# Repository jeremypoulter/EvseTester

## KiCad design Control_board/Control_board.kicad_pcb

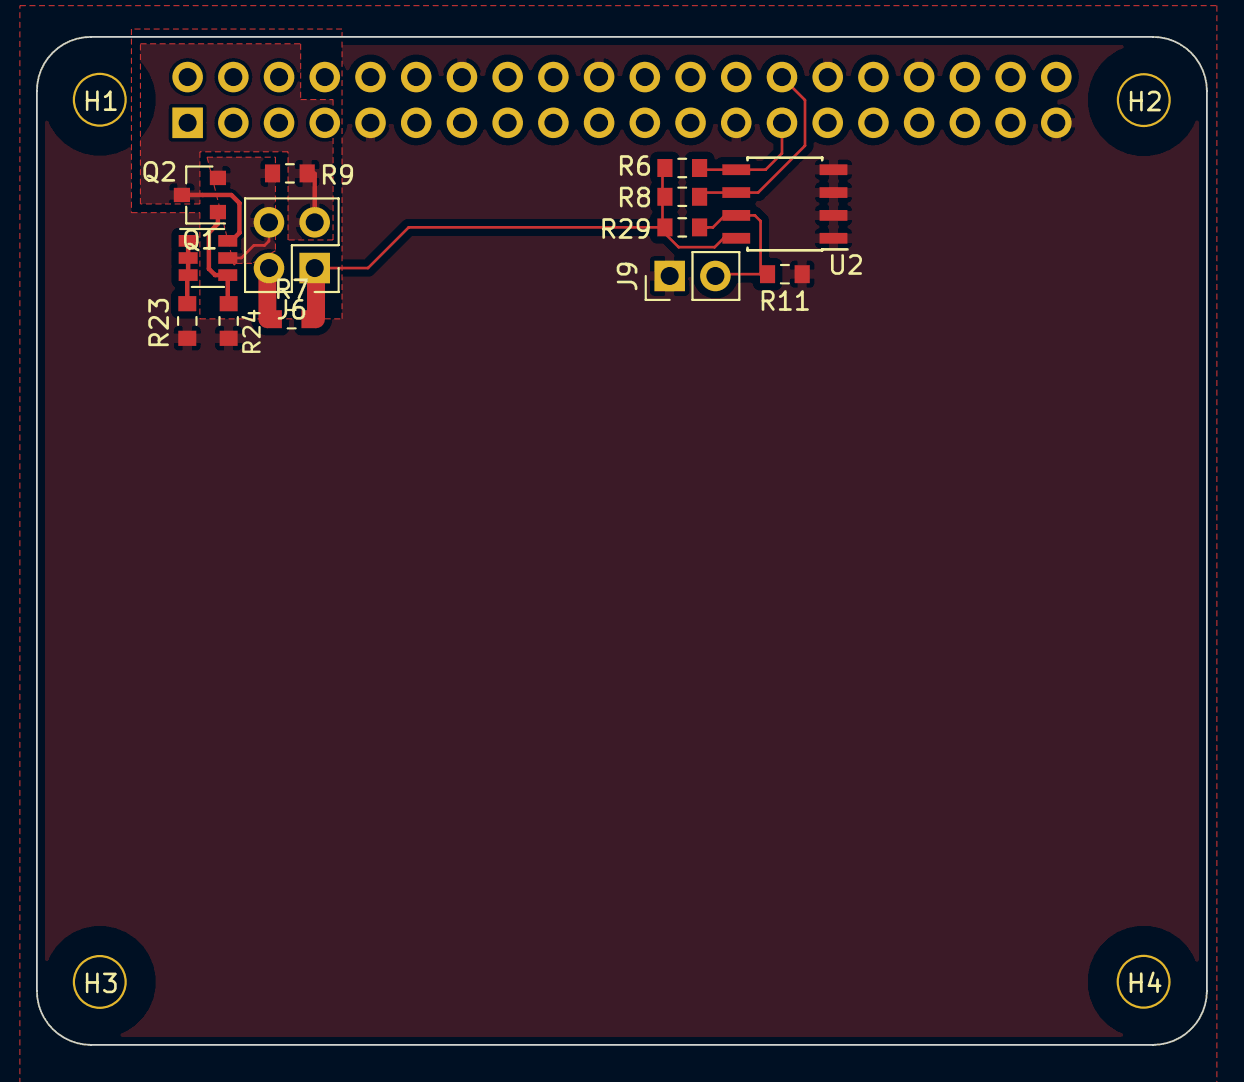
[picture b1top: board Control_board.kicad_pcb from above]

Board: 2 copper layers, 65.0 x 56.0 mm, 18 parts (1 on the bottom side), 10 nets.

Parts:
H1, H2, H3, H4: 3mm_Mounting_Hole; NPTH_3mm_ID
J3: 40HAT; PinSocket_2x20_P2.54mm_Vertical
J6: CONN_02X02; PinHeader_2x02_P2.54mm_Vertical
J9: CONN_01X02; PinHeader_1x02_P2.54mm_Vertical
Q1: DMG2305UX; SOT-23
Q2: DMMT5401; SOT-23-6
R6, R8: 3.9K; R_0603_1608Metric_Pad0.84x1.00mm_HandSolder
R7, R9, R11: DNP; R_0603_1608Metric_Pad0.84x1.00mm_HandSolder
R23, R29: 10K; R_0603_1608Metric_Pad0.84x1.00mm_HandSolder
R24: 47K; R_0603_1608Metric_Pad0.84x1.00mm_HandSolder
U2: CAT24C32; SOIC-8_3.9x4.9mm_P1.27mm

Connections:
/ID_SC_EEPROM: J3.28, R8.2, U2.6
/ID_SD_EEPROM: J3.27, R6.2, U2.5
/P3V3: J6.1, R6.1, R7.2, R8.1, R29.1, U2.8
/P3V3_HAT: J3.1, J6.2, R7.1
/P5V: J6.3, Q1.3, Q2.6, R9.2
/P5V_HAT: J3.2, J3.4, J6.4, Q1.2, Q2.5, R9.1
GND: J3.6, J3.9, J3.14, J3.20, J3.25, J3.30, J3.34, J3.39, J9.1, R11.2, R23.2, R24.2, U2.1, U2.2, U2.3, U2.4
unnamed: J9.2, R11.1, R29.2, U2.7
unnamed: Q1.1, Q2.4, R24.1
unnamed: Q2.1, Q2.2, Q2.3, R23.1

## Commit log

2022-02-12 Initial version (schematic only) of OpenEVSE test board
2022-02-12 Changed root page to A4 to match the rest
2022-02-12 Schematic PDFs
2022-02-13 Fixed AC paths
2022-02-13 Simple diagram of test setup
2022-02-13 Ignore Mac files
